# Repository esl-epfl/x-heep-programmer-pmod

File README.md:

# This repository contains the HEEP programmer PMOD
This PMOD pcb provides the following features:

1) An OpenOCD compatible JTAG programmer for debugging the RISC-V core
2) An 128 MBIT (Q)SPI flash chip as well as an [iceprog](https://github.com/YosysHQ/icestorm/tree/master/iceprog) compatible programmer for the flash (the programmer has been derived from [the excellent icebreaker board](https://github.com/icebreaker-fpga/icebreaker))
3) Two UARTs

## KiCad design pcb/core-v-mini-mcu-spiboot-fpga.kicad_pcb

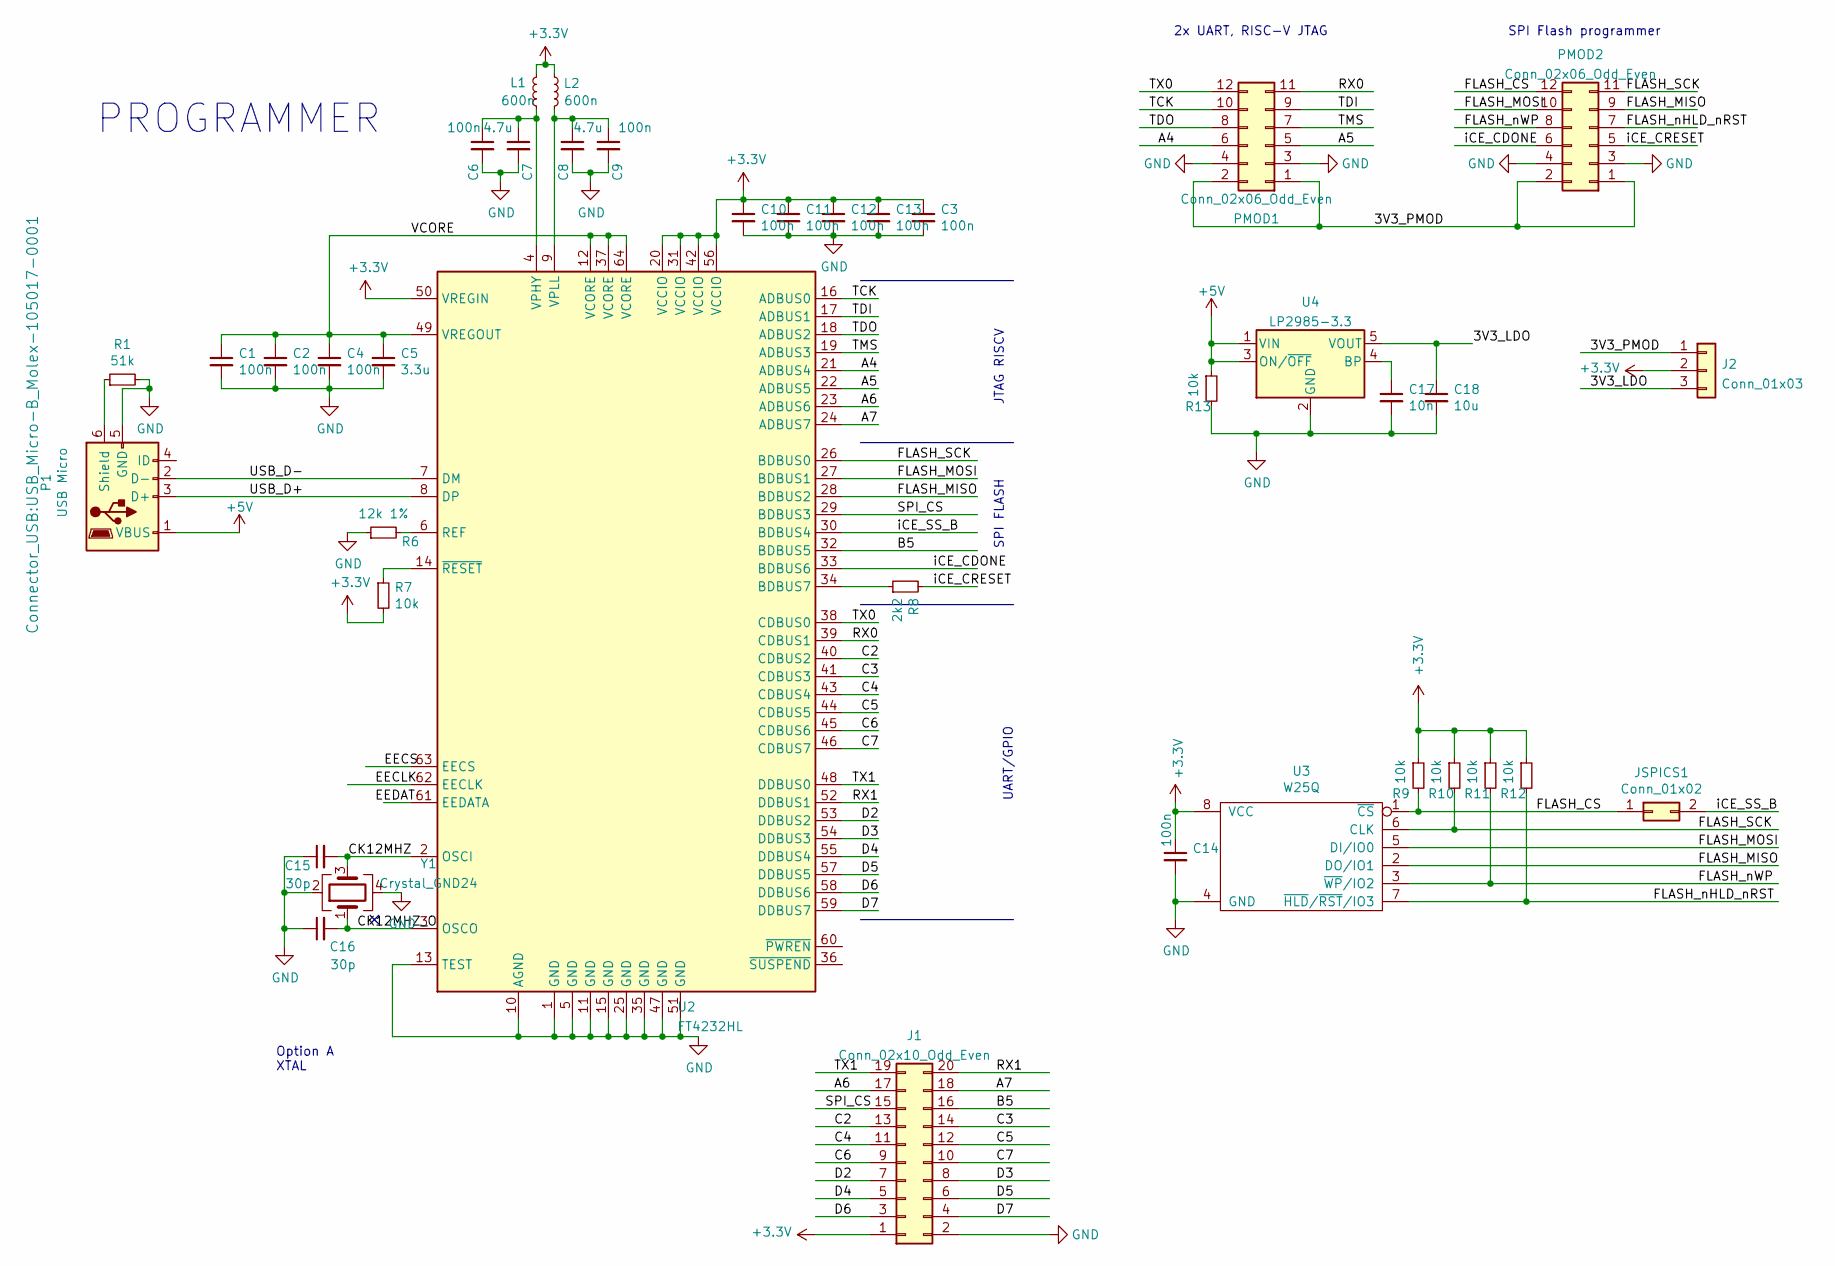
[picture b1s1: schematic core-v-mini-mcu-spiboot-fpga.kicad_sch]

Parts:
C1, C2, C3, C4, C6, C9, C10, C11, C12, C13, C14: 100n; C_0603_1608Metric; Mouser Part Number 80-C0805C104Z3V; Digikey Part Number 399-9158-1-ND
C5: 3.3u; C_0805_2012Metric; Mouser Part Number 80-C0805C335K8P; Digikey Part Number 399-3129-1-ND
C7, C8: 4.7u; C_0805_2012Metric; Mouser Part Number 80-C0805C475K9P; Digikey Part Number 399-3134-1-ND
C15, C16: 30p; C_0603_1608Metric; Mouser Part Number 80-C0805C104Z3V; Digikey Part Number 399-9158-1-ND
C17: 10n; C_0603_1608Metric; Mouser Part Number 80-C0805C104Z3V; Digikey Part Number 399-9158-1-ND
C18: 10u; C_0603_1608Metric; Mouser Part Number 80-C0805C104Z3V; Digikey Part Number 399-9158-1-ND
J1: Conn_02x10_Odd_Even; PinHeader_2x10_P2.54mm_Vertical
J2: Conn_01x03; PinHeader_1x03_P2.54mm_Vertical
JSPICS1: Conn_01x02; PinHeader_1x02_P2.54mm_Vertical; Digikey Part Number 2057-PH1-02-UA-ND
L1, L2: 600n; L_0805_2012Metric; Digikey Part Number 2035-1293-1-ND
P1: USB Micro; USB_Micro-B_Molex-105017-0001; Mouser Part Number 538-105017-0001; Digikey Part Number WM1399CT-ND
PMOD1, PMOD2: Conn_02x06_Odd_Even; PinHeader_2x06_P2.54mm_Horizontal
R1: 51k; R_0603_1608Metric; Mouser Part Number 660-RK73B1JTTD513J; Digikey Part Number 2019-RK73B1JTTD513JCT-ND
R6: 12k 1%; R_0603_1608Metric; Mouser Part Number 652-CR0603FX-1202ELF; Digikey Part Number 118-CR0603-FX-1202ELFCT-ND
R7, R9, R10, R11, R12, R13: 10k; R_0603_1608Metric; Mouser Part Number 667-ERJ-3GEYJ103V; Digikey Part Number P10KGCT-ND
R8: 2k2; R_0603_1608Metric; Mouser Part Number 667-ERJ-3GEYJ222V; Digikey Part Number P2.2KGCT-ND
U2: FT4232HL; LQFP-64_10x10mm_P0.5mm
U3: W25Q; SOIC-8_5.23x5.23mm_P1.27mm; Mouser Part Number 454-W25Q128JVSIMTR; Digikey Part Number W25Q128JVSIMCT-ND
U4: LP2985-3.3; SOT-23-5
Y1: Crystal_GND24; Crystal_SMD_3225-4Pin_3.2x2.5mm

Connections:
+3V3: C3.1, C10.1, C11.1, C12.1, C13.1, C14.1, J1.1, J2.2, L1.1, L2.1, R7.2, R9.1, R10.1, R11.1, R12.1, U2.20 (VCCIO), U2.31 (VCCIO), U2.42 (VCCIO), U2.50 (VREGIN), U2.56 (VCCIO), U3.8 (VCC)
+5V: P1.1 (VBUS), R13.1, U4.1 (VIN), U4.3 (ON/~OFF)
/3V3_LDO: C18.1, J2.3, U4.5 (VOUT)
/3V3_PMOD: J2.1, PMOD1.1, PMOD1.2, PMOD2.1, PMOD2.2
/A4: PMOD1.6, U2.21 (ADBUS4)
/A5: PMOD1.5, U2.22 (ADBUS5)
/A6: J1.17, U2.23 (ADBUS6)
/A7: J1.18, U2.24 (ADBUS7)
/B5: J1.16, U2.32 (BDBUS5)
/C2: J1.13, U2.40 (CDBUS2)
/C3: J1.14, U2.41 (CDBUS3)
/C4: J1.11, U2.43 (CDBUS4)
/C5: J1.12, U2.44 (CDBUS5)
/C6: J1.9, U2.45 (CDBUS6)
/C7: J1.10, U2.46 (CDBUS7)
/CK12MHZ: C15.2, U2.2 (OSCI), Y1.3
/CK12MHZ_O: C16.2, U2.3 (OSCO), Y1.1
/D2: J1.7, U2.53 (DDBUS2)
/D3: J1.8, U2.54 (DDBUS3)
/D4: J1.5, U2.55 (DDBUS4)
/D5: J1.6, U2.57 (DDBUS5)
/D6: J1.3, U2.58 (DDBUS6)
/D7: J1.4, U2.59 (DDBUS7)
/EECLK: U2.62 (EECLK)
/EECS: U2.63 (EECS)
/FLASH_CS: JSPICS1.1, PMOD2.12, R9.2, U3.1 (~CS)
/FLASH_MISO: PMOD2.9, U2.28 (BDBUS2), U3.2 (DO/IO1)
/FLASH_MOSI: PMOD2.10, U2.27 (BDBUS1), U3.5 (DI/IO0)
/FLASH_SCK: PMOD2.11, R10.2, U2.26 (BDBUS0), U3.6 (CLK)
/FLASH_nHLD_nRST: PMOD2.7, R12.2, U3.7 (~HLD/~RST/IO3)
/FLASH_nWP: PMOD2.8, R11.2, U3.3 (~WP/IO2)
/RX0: PMOD1.11, U2.39 (CDBUS1)
/RX1: J1.20, U2.52 (DDBUS1)
/SPI_CS: J1.15, U2.29 (BDBUS3)
/TCK: PMOD1.10, U2.16 (ADBUS0)
/TDI: PMOD1.9, U2.17 (ADBUS1)
/TDO: PMOD1.8, U2.18 (ADBUS2)
/TMS: PMOD1.7, U2.19 (ADBUS3)
/TX0: PMOD1.12, U2.38 (CDBUS0)
/TX1: J1.19, U2.48 (DDBUS0)
/USB_D+: P1.3 (D+), U2.8 (DP)
/USB_D-: P1.2 (D-), U2.7 (DM)
/VCORE: C1.1, C2.1, C4.1, C5.1, U2.12 (VCORE), U2.37 (VCORE), U2.49 (VREGOUT), U2.64 (VCORE)
/iCE_CDONE: PMOD2.6, U2.33 (BDBUS6)
/iCE_CRESET: PMOD2.5, R8.2
/iCE_SS_B: JSPICS1.2, U2.30 (BDBUS4)
GND: C1.2, C2.2, C3.2, C4.2, C5.2, C6.2, C7.2, C8.2, C9.2, C10.2, C11.2, C12.2, C13.2, C14.2, C15.1, C16.1, C17.2, C18.2, J1.2, P1.5 (GND), PMOD1.3, PMOD1.4, PMOD2.3, PMOD2.4, R1.2, R6.1, R13.2, U2.1 (GND), U2.5 (GND), U2.10 (AGND), U2.11 (GND), U2.13 (TEST), U2.15 (GND), U2.25 (GND), U2.35 (GND), U2.47 (GND), U2.51 (GND), U3.4 (GND), U4.2 (GND), Y1.2, Y1.4
unnamed: C6.1, C7.1, L1.2, U2.4 (VPHY)
unnamed: C8.1, C9.1, L2.2, U2.9 (VPLL)
unnamed: C17.1, U4.4 (BP)
unnamed: P1.6 (Shield), R1.1
unnamed: R6.2, U2.6 (REF)
unnamed: R7.1, U2.14 (~RESET)
unnamed: R8.1, U2.34 (BDBUS7)

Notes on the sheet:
SPI FLASH
SPI Flash programmer
JTAG RISCV
UART/GPIO
Option A XTAL
2x UART, RISC-V JTAG
PROGRAMMER

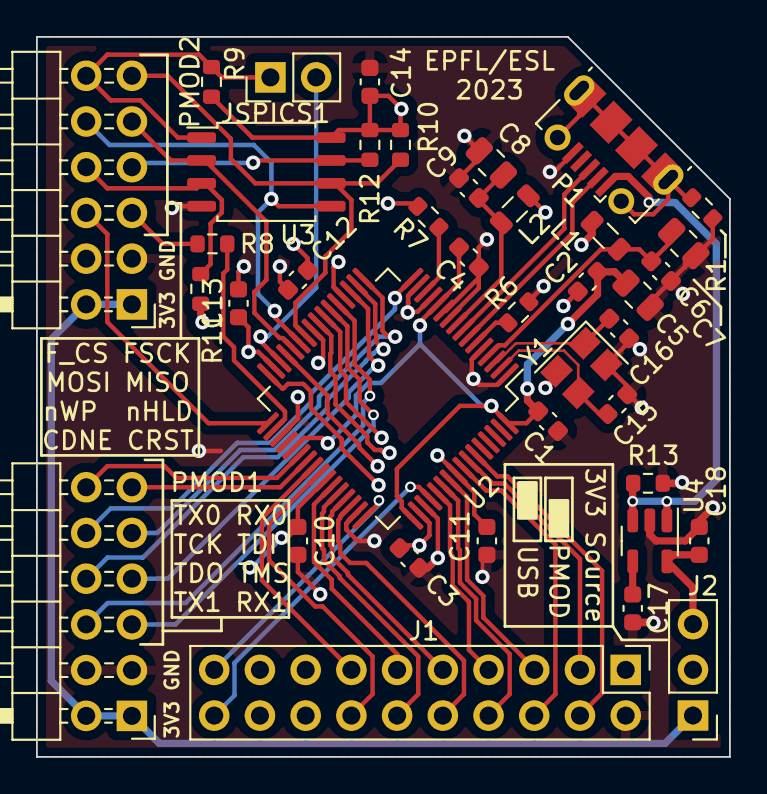
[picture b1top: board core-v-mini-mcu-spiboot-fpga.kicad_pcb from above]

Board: 4 copper layers, 38.5 x 40.0 mm, 39 parts (0 on the bottom side), 52 nets.

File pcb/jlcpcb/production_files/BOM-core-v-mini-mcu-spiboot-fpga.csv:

Comment,Designator,Footprint,LCSC
10n,C17,C_0603_1608Metric,C100042
51k,R1,R_0603_1608Metric,C107231
30p,"C15,C16",C_0603_1608Metric,C113797
USB Micro,P1,USB_Micro-B_Molex-105017-0001,C132563
3.3u,C5,C_0805_2012Metric,C159781
4.7u,"C7,C8",C_0805_2012Metric,C1779
10u,C18,C_0603_1608Metric,C19702
12k 1%,R6,R_0603_1608Metric,C22790
W25Q,U3,SOIC-8_5.23x5.23mm_P1.27mm,C2613930
600n,"L1,L2",L_0805_2012Metric,C280244
100n,"C1,C10,C11,C12,C13,C14,C2,C3,C4,C6,C9",C_0603_1608Metric,C30926
2k2,R8,R_0603_1608Metric,C4190
FT4232HL,U2,LQFP-64_10x10mm_P0.5mm,C56742
Crystal_GND24,Y1,Crystal_SMD_3225-4Pin_3.2x2.5mm,C9002
LP2985-3.3,U4,SOT-23-5,C95414
10k,"R10,R11,R12,R13,R7,R9",R_0603_1608Metric,C98220
Conn_01x03,J2,PinHeader_1x03_P2.54mm_Vertical,
Conn_02x10_Odd_Even,J1,PinHeader_2x10_P2.54mm_Vertical,
Conn_01x02,JSPICS1,PinHeader_1x02_P2.54mm_Vertical,
Conn_02x06_Odd_Even,PMOD1,PinHeader_2x06_P2.54mm_Horizontal,
Conn_02x06_Odd_Even,PMOD2,PinHeader_2x06_P2.54mm_Horizontal,

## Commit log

2022-06-17 pcb added
2022-06-17 basic readme added
2022-06-17 some documentation
2022-06-21 Revision 2: Converted to the available 56 pin QFN package, added missing oscillator
2022-06-30 QFN version
2023-01-16 Programmer reverted to LQFP package, production files for JLCPCB order added.
2023-03-06 pdf & picture recreated
2023-03-06 CC-BY-SA 4.0 added
2023-03-06 Update README.md
    Credit to Icebreaker added
2023-03-06 Update README.md
    typo
